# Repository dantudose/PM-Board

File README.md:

# PM-Board

## Embedded development board with ATmega324P

This is a development board supporting the ATmega324P microcontroller. It is fully Arduino-compatible and it comes with the following features:
* LSM9DS0 9-axis inertial sensor (accelerometer, gyroscope and magnetometer)
* MPL3115 baro-altimeter sensor
* Ambient temperature and light sensors
* 128x160 ST7735 color LCD display with SD card reader 
* RGB LED
* 16x02 character LCD display
* GPIO LEDs and pushbuttons
* JTAG and ISP connectors
* USB programming and data interface

<div id="cover">

</div>

## Repository Contents

* **/Code** - Test code for the board (PlatformIO)
* **/Hardware** - Eagle design files (.brd, .sch)
* **/Images** - Board images
* **/bin** - Binaries (board bootloader)

## Programming

### avr-gcc & Makefile

#### Bootloader
The board comes pre-loaded with a bootloader. If you need to re-write it, connect an AVR-ISP or JTAG to the corresponding port and burn the <a href="https://github.com/dantudose/PM-Board/tree/main/bin">bootloader</a> .hex file with _atmega324p_ as a target and the following fuse settings:

<table>
<thead>
  <tr>
    <th>Fuse</th>
    <th>Value</th>
  </tr>
</thead>
<tbody>
  <tr>
    <td>HIGH</td>
    <td>0xDA</td>
  </tr>
  <tr>
    <td>LOW</td>
    <td>0xD7</td>
  </tr>
  <tr>
    <td>EXT</td>
    <td>0XFD</td>
  </tr>
</tbody>
</table>

#### Writing a simple Hello World

Install avr-gcc on your machine. There are various tutorials on how to do this. Here are some examples, depending on your OS type:
* <a href="https://tinusaur.com/guides/avr-gcc-toolchain/">Windows</a>
* <a href="https://baremetalmicro.com/tutorial_avr_toolchain/03-Install-on-Ubuntu-Linux.html">Linux</a>
* <a href="https://wellys.com/posts/avr_c_macos/">Mac</a>

Copy this code into your favourite code editor and save the file as "hello.c":

```cpp
#include <avr/io.h>
#include <util/delay.h>
 
int main() {
	/* Setting PC0 as output */
	DDRC |= (1 << PC0);
 
	while(1) {
                /* Toggle pin state */
		PORTC ^= (1 << PC0);
 
                _delay_ms(500);
	}
 
	return 0;
}

```
To build and upload, you can use the following Makefile. Edit the port to correspond with your OS and serial port name:

```Makefile
# Linux
PORT ?= /dev/ttyUSB0
# Windows
# PORT ?= COM1
 
all: hello.hex
 
hello.hex: hello.elf
	avr-objcopy  -j .text -j .data -O ihex $^ $@
	avr-size hello.elf
 
hello.elf: hello.c
	avr-g++ -mmcu=atmega324p -DF_CPU=12000000 -Os -Wall -o $@ $^
 
upload: hello.hex
	avrdude -c urclock -P $(PORT) -b 57600 -p atmega324p -D -xnometadata -U flash:w:$<:a
 
clean:
	rm -rf hello.elf hello.hex
```

From your command line call _> make all_ (generates hello.hex) and then _> make upload_.

### Arduino

The board can be programmed using <a href="https://github.com/MCUdude/MightyCore">Mighty-Core</a>. 

Follow the "How to install" guide on their github page and use the following settings when burning the bootloader and uploading a sketch:

### PlatformIO (VSCode)

Use the /Code project as reference. 

## Board Pinout

#### LCD Displays

<table>
<thead>
  <tr>
    <th>Character LCD</th>
    <th>GPIO Pin</th>
    <th>Arduino Pin</th>
    <th></th>
    <th>Graphical LCD</th>
    <th>GPIO Pin</th>
    <th>Arduino Pin</th>
  </tr>
</thead>
<tbody>
  <tr>
    <td>RS</td>
    <td>PC0</td>
    <td>16</td>
    <td></td>
    <td>CS</td>
    <td>PB0</td>
    <td>0</td>
  </tr>
  <tr>
    <td>RW</td>
    <td>PC1</td>
    <td>17</td>
    <td></td>
    <td>RST</td>
    <td>PB1</td>
    <td>1</td>
  </tr>
  <tr>
    <td>EN</td>
    <td>PC2</td>
    <td>18</td>
    <td></td>
    <td>A0</td>
    <td>PB4</td>
    <td>4</td>
  </tr>
  <tr>
    <td>D4</td>
    <td>PC3</td>
    <td>19</td>
    <td></td>
    <td>SDA</td>
    <td>PB5</td>
    <td>5</td>
  </tr>
  <tr>
    <td>D5</td>
    <td>PC4</td>
    <td>20</td>
    <td></td>
    <td>SCK</td>
    <td>PB7</td>
    <td>7</td>
  </tr>
  <tr>
    <td>D6</td>
    <td>PC5</td>
    <td>21</td>
    <td></td>
    <td>Backlight</td>
    <td>PA7</td>
    <td>31</td>
  </tr>
  <tr>
    <td>D7</td>
    <td>PC6</td>
    <td>22</td>
    <td></td>
    <td></td>
    <td></td>
    <td></td>
  </tr>
  <tr>
    <td>Backlight</td>
    <td>PC7</td>
    <td>23</td>
    <td></td>
    <td></td>
    <td></td>
    <td></td>
  </tr>
</tbody>
</table>

#### I2C Sensors & Bus Addresses

<table style="float: left; width: 584.312px;">
<tbody>
<tr>
<td style="width: 76px;">&nbsp;<strong>I2C</strong></td>
<td style="width: 103px;"><strong>&nbsp;GPIO Pin</strong>&nbsp;</td>
<td style="width: 94px;"><strong>&nbsp;Arduino Pin</strong>&nbsp;</td>
<td style="width: 35px;">&nbsp;</td>
<td style="width: 98px;"><strong>&nbsp;Chip</strong>&nbsp;</td>
<td style="width: 162.312px;"><strong>&nbsp;Address</strong>&nbsp;</td>
</tr>
<tr>
<td style="width: 76px;">&nbsp;I2C Enable&nbsp;</td>
<td style="width: 103px;">&nbsp;PA6</td>
<td style="width: 94px;">&nbsp;30</td>
<td style="width: 35px;">&nbsp;</td>
<td style="width: 98px;">&nbsp;LSM9DS0&nbsp;</td>
<td style="width: 162.312px;">&nbsp;0x1D (XM) 0x6B (G)</td>
</tr>
<tr>
<td style="width: 76px;">&nbsp;SCL&nbsp;</td>
<td style="width: 103px;">&nbsp;PC0&nbsp;</td>
<td style="width: 94px;">&nbsp;16</td>
<td style="width: 35px;">&nbsp;</td>
<td style="width: 98px;">&nbsp;MPL3115A2&nbsp;</td>
<td style="width: 162.312px;">&nbsp;0x60&nbsp;</td>
</tr>
<tr>
<td style="width: 76px;">&nbsp;SDA&nbsp;</td>
<td style="width: 103px;">&nbsp;PC1&nbsp;</td>
<td style="width: 94px;">&nbsp;17&nbsp;</td>
<td style="width: 35px;">&nbsp;</td>
<td style="width: 98px;">&nbsp;</td>
<td style="width: 162.312px;">&nbsp;</td>
</tr>
</tbody>
</table>
<!-- DivTable.com -->

#### SD Card

<table style="float: left;">
<tbody>
<tr>
<td>&nbsp;<b> </b>&nbsp;</td>
<td>&nbsp;<b>GPIO Pin</b>&nbsp;</td>
<td>&nbsp;<b>Arduino Pin</b>&nbsp;</td>
</tr>
<tr>
<td>&nbsp;CS</td>
<td>&nbsp;PA2</td>
<td>&nbsp;26</td>
</tr>
<tr>
<td>&nbsp;MOSI&nbsp;</td>
<td>&nbsp;PB5&nbsp;</td>
<td>&nbsp;5&nbsp;</td>
</tr>
<tr>
<td>&nbsp;MISO&nbsp;</td>
<td>&nbsp;PB6&nbsp;</td>
<td>&nbsp;6&nbsp;</td>
</tr>
<tr>
<td>&nbsp;SCK&nbsp;</td>
<td>&nbsp;PB7&nbsp;</td>
<td>&nbsp;7&nbsp;</td>
</tr>
</tbody>
</table>
<!-- DivTable.com -->

#### RGB LED

<table class="tg">
<thead>
  <tr>
    <th class="tg-amwm"> </th>
    <th class="tg-amwm">GPIO Pin</th>
    <th class="tg-amwm">Arduino Pin</th>
  </tr>
</thead>
<tbody>
  <tr>
    <td class="tg-hmp3">Red</td>
    <td class="tg-hmp3">PD5</td>
    <td class="tg-hmp3">13</td>
  </tr>
  <tr>
    <td class="tg-0lax">Green</td>
    <td class="tg-0lax">PD7</td>
    <td class="tg-0lax">15</td>
  </tr>
  <tr>
    <td class="tg-hmp3">Blue</td>
    <td class="tg-hmp3">PB3</td>
    <td class="tg-hmp3">3</td>
  </tr>
</tbody>
</table>

### Miscellaneous

<table class="tg">
<thead>
  <tr>
    <th class="tg-0lax"></th>
    <th class="tg-amwm">GPIO Pin</th>
    <th class="tg-amwm">Arduino Pin</th>
  </tr>
</thead>
<tbody>
  <tr>
    <td class="tg-0lax">Temperature Sensor</td>
    <td class="tg-0lax">PA0</td>
    <td class="tg-0lax">A0</td>
  </tr>
  <tr>
    <td class="tg-0lax">Ambient Light Sensor</td>
    <td class="tg-0lax">PA1</td>
    <td class="tg-0lax">A1</td>
  </tr>
  <tr>
    <td class="tg-0lax">BUTTON 1 (PB2)</td>
    <td class="tg-0lax">PB2</td>
    <td class="tg-0lax">2</td>
  </tr>
  <tr>
    <td class="tg-0lax">BUTTON 2 (PD6)</td>
    <td class="tg-0lax">PD6</td>
    <td class="tg-0lax">14</td>
  </tr>
  <tr>
    <td class="tg-0lax">Buttons (BTN1 - 6)</td>
    <td class="tg-0lax">PA5</td>
    <td class="tg-0lax">A5</td>
  </tr>
  <tr>
    <td class="tg-0lax">Speaker</td>
    <td class="tg-0lax">PD4</td>
    <td class="tg-0lax">12</td>
  </tr>
</tbody>
</table>

## License Information

This product is _**open source**_! 

Please review the LICENSE file for license information. 

Distributed as-is; no warranty is given.

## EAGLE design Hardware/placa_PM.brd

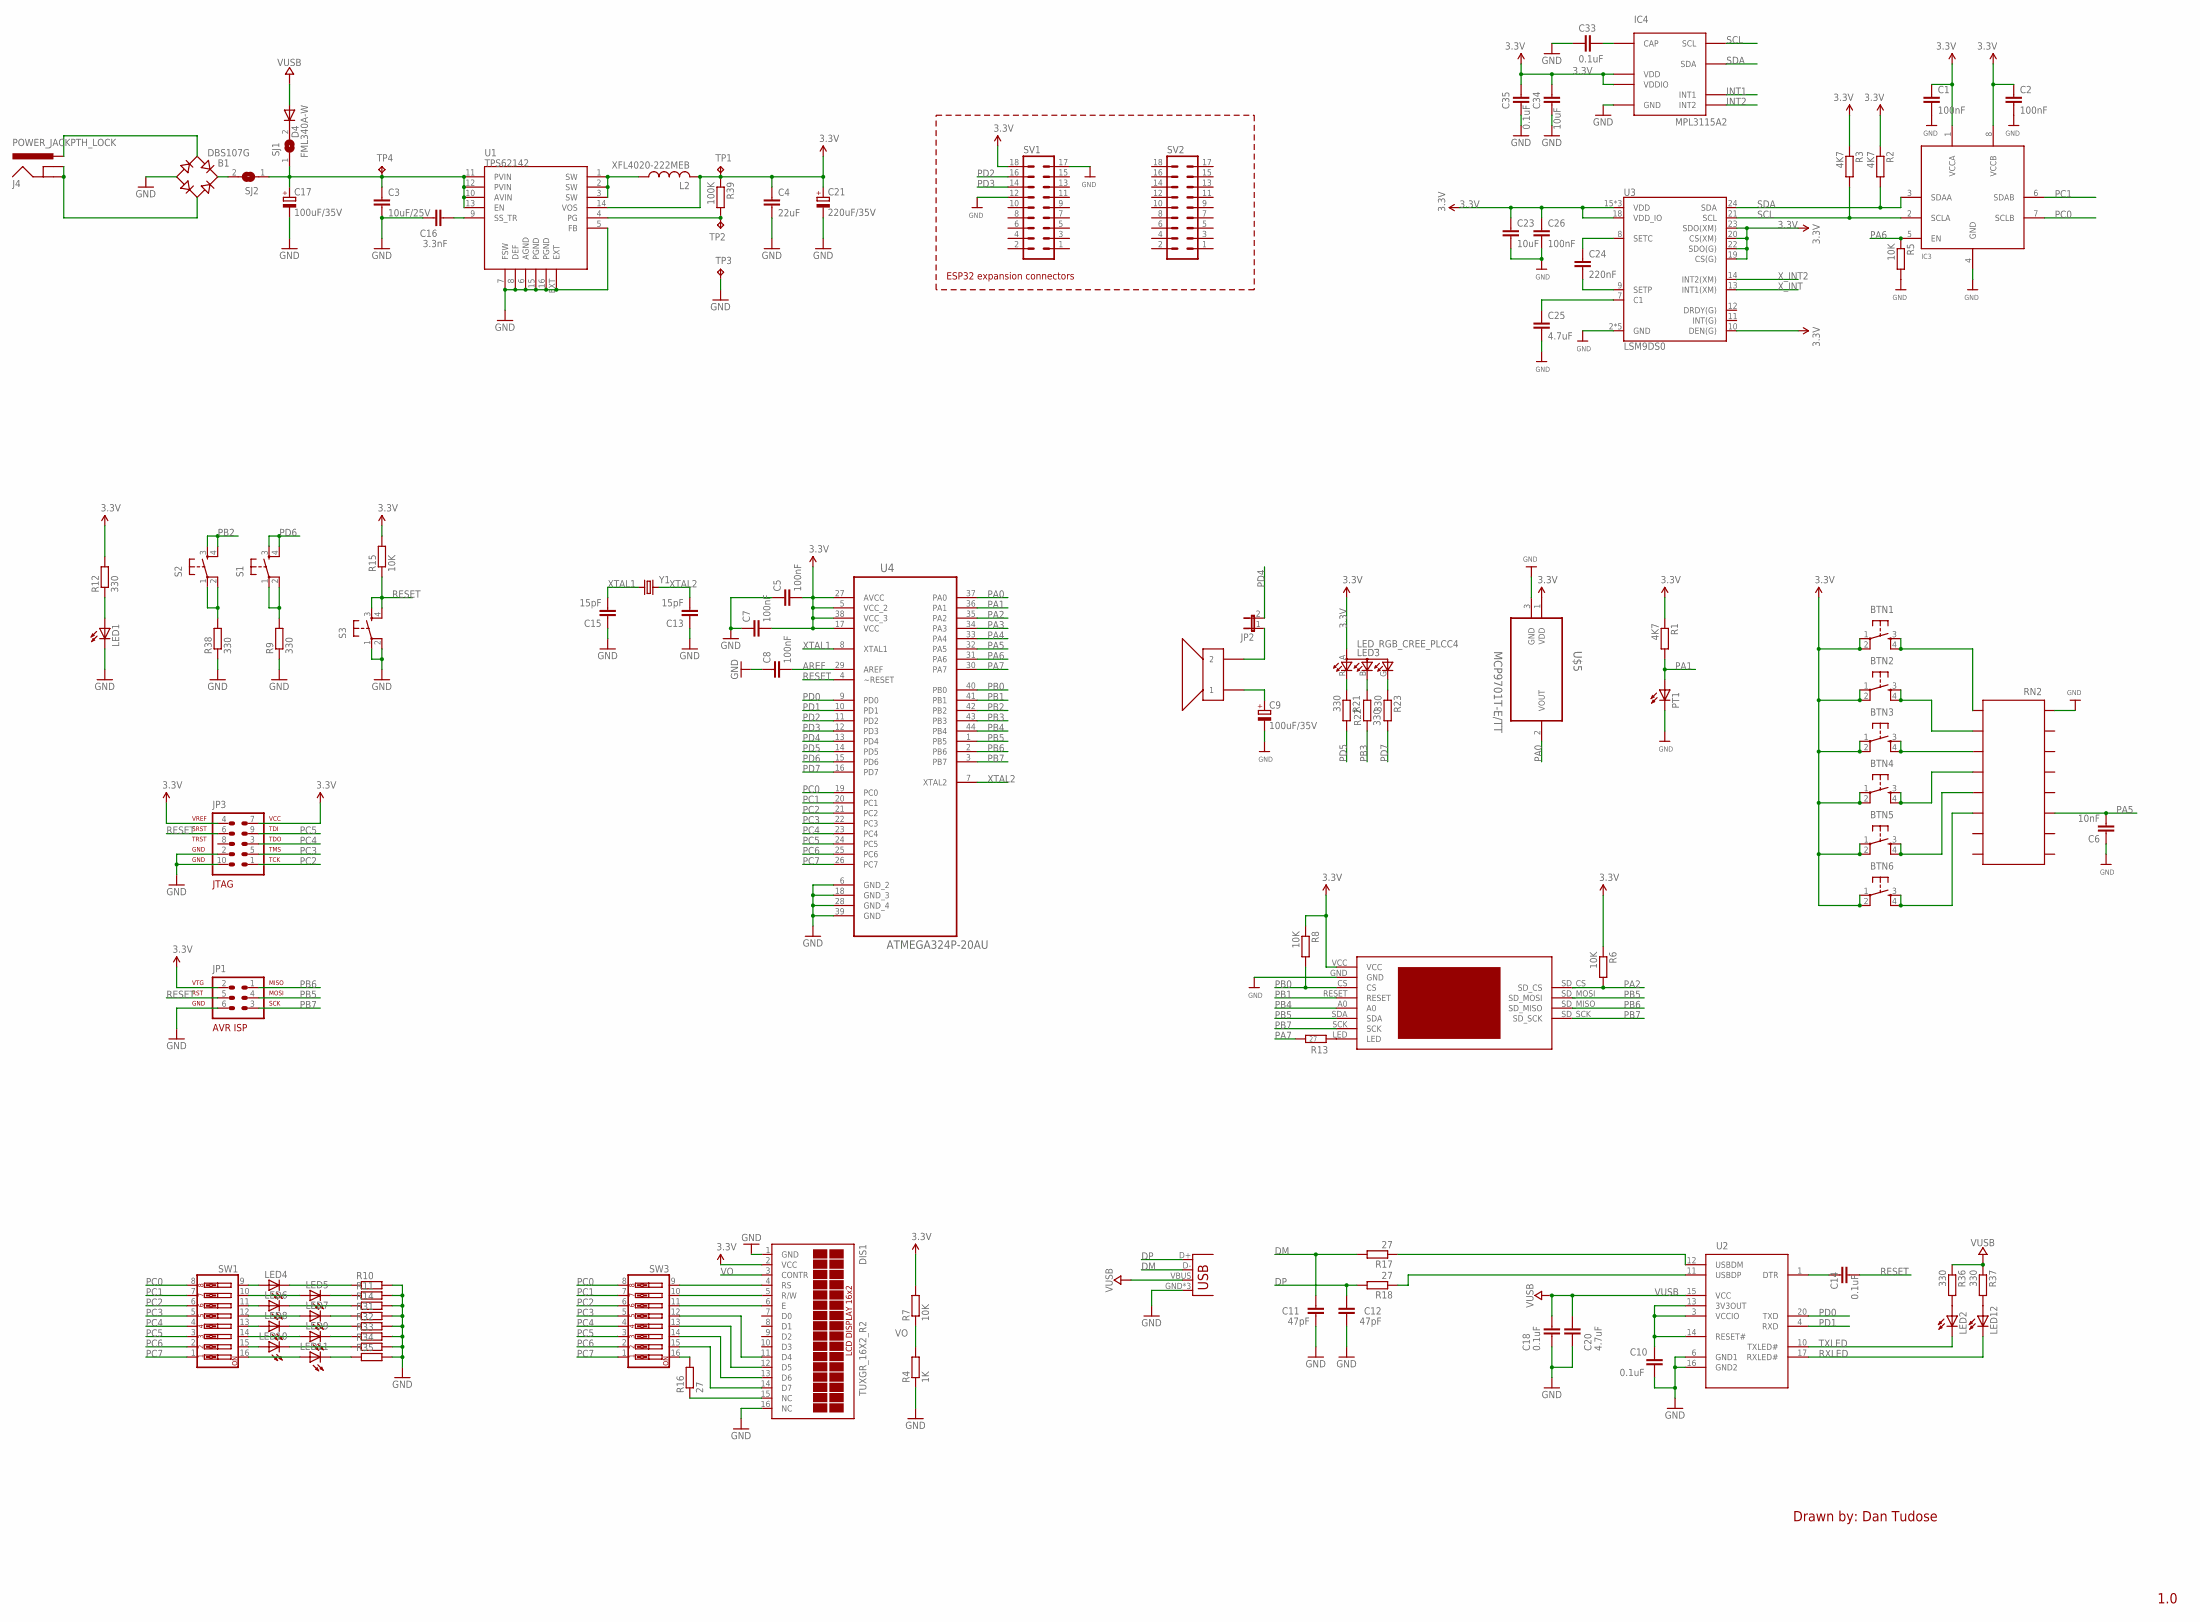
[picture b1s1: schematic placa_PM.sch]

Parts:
B1: DBS107G; DBS
BTN1, BTN2, BTN3, BTN4, BTN5, BTN6: TAC_SWITCHPTH; TACTILE-PTH
C1, C2, C5, C7, C8, C26: 100nF; C0402
C3: 10uF/25V; C1210
C4: 22uF; C1206
C6: 10nF; C0402
C9, C17: 100uF/35V; UD-6,3X7,7_NICHICON
C10, C14, C18: 0.1uF; C0402
C11, C12: 47pF; C0402
C13, C15: 15pF; C0402
C16: 3.3nF; C0603
C20, C25: 4.7uF; C0603
C21: 220uF/35V; UD-6,3X7,7_NICHICON
C23: 10uF; C0402
C24: 220nF; C0402
C33, C35: 0.1uF; 0402-CAP
C34: 10uF; 0402-CAP
D4: FML340A-W; DO-214AC
DIS1: TUXGR_16X2_R2
IC3: TCA9803VSS; VSSOP8
IC4: MPL3115A2; LGA8R125P0X4_500X300X120
J3: USBPTH; USB-B-PTH
J4: POWER_JACKPTH_LOCK; POWER_JACK_PTH_LOCK
JP1: AVR-ISP-6
JP2: JP1E; JP1
JP3: AVR-JTAG-10
L2: XFL4020-222MEB; XFL4020
LED1: LEDCHIPLED_0603; CHIPLED_0603
LED2, LED4, LED5, LED6, LED7, LED8, LED9, LED10, LED11, LED12: LEDCHIP-LED0603; CHIP-LED0603
LED3: LED_RGB_CREE_PLCC4; P-LCC-4-4
PT1: LEDSML0805; SML0805
R1, R2, R3: 4K7; R0402
R4: 1K; R0402
R5, R6, R7, R8, R15: 10K; R0402
R9, R12, R21, R22, R23, R36, R37, R38: 330; R0402
R10, R11, R14, R31, R32, R33, R34, R35: R-EU_R0402; R0402
R13, R16, R17, R18: 27; R0603
R39: 100K; R0402
RN2: 4816P-R2R; 4816P
S1, S2, S3: TAC_SWITCHPTH; TACTILE-PTH
SJ1, SJ2: SJ
SV1, SV2: MA09-2
SW1, SW3: SW_DIP-8; EDG-08
TP1, TP2, TP3, TP4: TPB1,27; B1,27
U1: TPS62142; QFN16-3X3MM_1:1_V03
U2: FT231XS; SSOP20
U3: LSM9DS0; LGA-24
U4: ATMEGA324P-20AU; QFP80P1200X1200X120-44N
U$5: MCP9701T-E/TT; SOT95P237X112-3N
U$6: CVS-3108; SPK
U$8: LCD128X160
Y1: CRYSTAL5X3; CRYSTAL-SMD-5X3

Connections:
3.3V: BTN1.1, BTN1.2, BTN2.1, BTN2.2, BTN3.1, BTN3.2, BTN4.1, BTN4.2, BTN5.1, BTN5.2, BTN6.1, BTN6.2, C1.1, C2.1, C4.1, C5.2, C7.2, C21.+, C23.1, C26.1, C34.2, C35.2, DIS1.2 (VCC), IC3.1 (VCCA), IC3.8 (VCCB), IC4.1 (VDD), IC4.4 (VDDIO), JP1.2, JP3.4, JP3.7, L2.P$2 (2), LED3.A (A2), R1.1, R2.1, R3.1, R6.1, R7.2, R8.1, R12.2, R15.2, R39.1, SV1.18, TP1.TP, U1.14 (VOS), U3.10 (DEN(G)), U3.15 (VDD), U3.16 (VDD), U3.17 (VDD), U3.18 (VDD_IO), U3.19 (CS(G)), U3.20 (CS(XM)), U3.22 (SDO(G)), U3.23 (SDO(XM)), U4.5 (VCC_2), U4.17 (VCC), U4.27 (AVCC), U4.38 (VCC_3), U$5.1 (VDD), U$8.VCC
AREF: C8.2, U4.29 (AREF)
DM: C11.2, J3.D-, R17.2
DP: C12.2, J3.D+, R18.2
GND: B1.-, C1.2, C2.2, C3.2, C4.2, C5.1, C6.1, C7.1, C8.1, C9.-, C10.2, C11.1, C12.1, C13.1, C15.1, C16.1, C17.-, C18.2, C20.2, C21.-, C23.2, C25.2, C26.2, C33.1, C34.1, C35.1, DIS1.1 (GND), DIS1.16 (NC), IC3.4 (GND), IC4.3 (GND), J3.GND, J3.P$1 (GND), J3.P$2 (GND), JP1.6, JP3.2, JP3.10, LED1.C, PT1.C, R4.1, R5.2, R9.1, R10.2, R11.2, R14.2, R31.2, R32.2, R33.2, R34.2, R35.2, R38.1, RN2.9, S3.1, S3.2, SV1.12, SV1.17, TP3.TP, U1.5 (FB), U1.6 (AGND), U1.7 (FSW), U1.8 (DEF), U1.15 (PGND), U1.16 (PGND), U1.EXT, U2.6 (GND1), U2.16 (GND2), U3.2 (GND), U3.3 (GND), U3.4 (GND), U3.5 (GND), U3.6 (GND), U4.6 (GND_2), U4.18 (GND_3), U4.28 (GND_4), U4.39 (GND), U$5.3 (GND), U$8.GND
INT1: IC4.6 (INT1)
INT2: IC4.5 (INT2)
unnamed: BTN1.3, BTN1.4, RN2.8
unnamed: LED1.A, R12.1
unnamed: JP2.1, U$6.P$2 (2)
unnamed: BTN2.3, BTN2.4, RN2.7
unnamed: DIS1.4 (RS), SW3.9
unnamed: C9.+, U$6.P$1 (1)
unnamed: DIS1.5 (R/W), SW3.10
unnamed: DIS1.15 (NC), R16.1
unnamed: R38.2, S2.1, S2.2
unnamed: D4.C, SJ1.2
unnamed: B1.AC1, J4.PWR
unnamed: B1.AC2, J4.GND, J4.GNDBREAK
unnamed: C3.1, C17.+, SJ1.1, SJ2.1, TP4.TP, U1.10 (AVIN), U1.11 (PVIN), U1.12 (PVIN), U1.13 (EN)
unnamed: BTN3.3, BTN3.4, RN2.6
unnamed: BTN4.3, BTN4.4, RN2.5
unnamed: DIS1.6 (E), SW3.11
unnamed: R9.2, S1.1, S1.2
unnamed: B1.+, SJ2.2
unnamed: BTN5.3, BTN5.4, RN2.4
unnamed: BTN6.3, BTN6.4, RN2.3
unnamed: R13.2, U$8.LED
unnamed: LED3.R (CRED), R21.1
unnamed: LED3.B (CBLUE), R22.2
unnamed: C14.1, U2.1 (DTR)
unnamed: C33.2, IC4.2 (CAP)
unnamed: LED3.G (CGREEN), R23.1
unnamed: C24.1, U3.8 (SETC)
unnamed: C24.2, U3.9 (SETP)
unnamed: C25.1, U3.7 (C1)
unnamed: DIS1.11 (D4), SW3.12
unnamed: DIS1.12 (D5), SW3.13
unnamed: C16.2, U1.9 (SS_TR)
unnamed: DIS1.13 (D6), SW3.14
unnamed: DIS1.14 (D7), SW3.15
unnamed: R16.2, SW3.16
unnamed: LED4.A, SW1.9
unnamed: LED6.A, SW1.11
unnamed: LED8.A, SW1.13
unnamed: LED10.A, SW1.15
unnamed: LED11.A, SW1.16
unnamed: LED9.A, SW1.14
unnamed: LED7.A, SW1.12
unnamed: LED5.A, SW1.10
unnamed: LED4.C, R10.1
unnamed: LED5.C, R11.1
unnamed: LED6.C, R14.1
unnamed: LED7.C, R31.1
unnamed: LED8.C, R32.1
unnamed: LED9.C, R33.1
unnamed: LED10.C, R34.1
unnamed: LED11.C, R35.1
unnamed: C10.1, U2.3 (VCCIO), U2.13 (3V3OUT), U2.14 (RESET#)
unnamed: R17.1, U2.12 (USBDM)
unnamed: R18.1, U2.11 (USBDP)
unnamed: LED2.A, R36.2
unnamed: LED12.A, R37.2
unnamed: L2.P$1 (1), U1.1 (SW), U1.2 (SW), U1.3 (SW)
unnamed: R39.2, TP2.TP, U1.4 (PG)
PA0: U4.37 (PA0), U$5.2 (VOUT)
PA1: PT1.A, R1.2, U4.36 (PA1)
PA2: R6.2, U4.35 (PA2), U$8.SD_CS
PA3: U4.34 (PA3)
PA4: U4.33 (PA4)
PA5: C6.2, RN2.14, U4.32 (PA5)
PA6: IC3.5 (EN), R5.1, U4.31 (PA6)
PA7: R13.1, U4.30 (PA7)
PB0: R8.2, U4.40 (PB0), U$8.CS
PB1: U4.41 (PB1), U$8.RESET
PB2: S2.3, S2.4, U4.42 (PB2)
PB3: R22.1, U4.43 (PB3)
PB4: U4.44 (PB4), U$8.A0
PB5: JP1.4, U4.1 (PB5), U$8.SDA, U$8.SD_MOSI
PB6: JP1.1, U4.2 (PB6), U$8.SD_MISO
PB7: JP1.3, U4.3 (PB7), U$8.SCK, U$8.SD_SCK
PC0: IC3.7 (SCLB), SW1.8, SW3.8, U4.19 (PC0)
PC1: IC3.6 (SDAB), SW1.7, SW3.7, U4.20 (PC1)
PC2: JP3.1, SW1.6, SW3.6, U4.21 (PC2)
PC3: JP3.5, SW1.5, SW3.5, U4.22 (PC3)
PC4: JP3.3, SW1.4, SW3.4, U4.23 (PC4)
PC5: JP3.9, SW1.3, SW3.3, U4.24 (PC5)
PC6: SW1.2, SW3.2, U4.25 (PC6)
PC7: SW1.1, SW3.1, U4.26 (PC7)
PD0: U2.20 (TXD), U4.9 (PD0)
PD1: U2.4 (RXD), U4.10 (PD1)
PD2: SV1.16, U4.11 (PD2)
PD3: SV1.14, U4.12 (PD3)
PD4: JP2.2, U4.13 (PD4)
PD5: R21.2, U4.14 (PD5)
PD6: S1.3, S1.4, U4.15 (PD6)
PD7: R23.2, U4.16 (PD7)
RESET: C14.2, JP1.5, JP3.6, R15.1, S3.3, S3.4, U4.4 (~RESET)
RXLED: LED12.C, U2.17 (RXLED#)
SCL: IC3.2 (SCLA), IC4.8 (SCL), R3.2, U3.21 (SCL)
SDA: IC3.3 (SDAA), IC4.7 (SDA), R2.2, U3.24 (SDA)
TXLED: LED2.C, U2.10 (TXLED#)
VO: DIS1.3 (CONTR), R4.2, R7.1
VUSB: C18.1, C20.1, D4.A, J3.VBUS, R36.1, R37.1, U2.15 (VCC)
XTAL1: C15.2, U4.8 (XTAL1), Y1.1
XTAL2: C13.2, U4.7 (XTAL2), Y1.3 (2)
X_INT: U3.13 (INT1(XM))
X_INT2: U3.14 (INT2(XM))

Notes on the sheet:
ESP32 expansion connectors
Drawn by: Dan Tudose
1.0

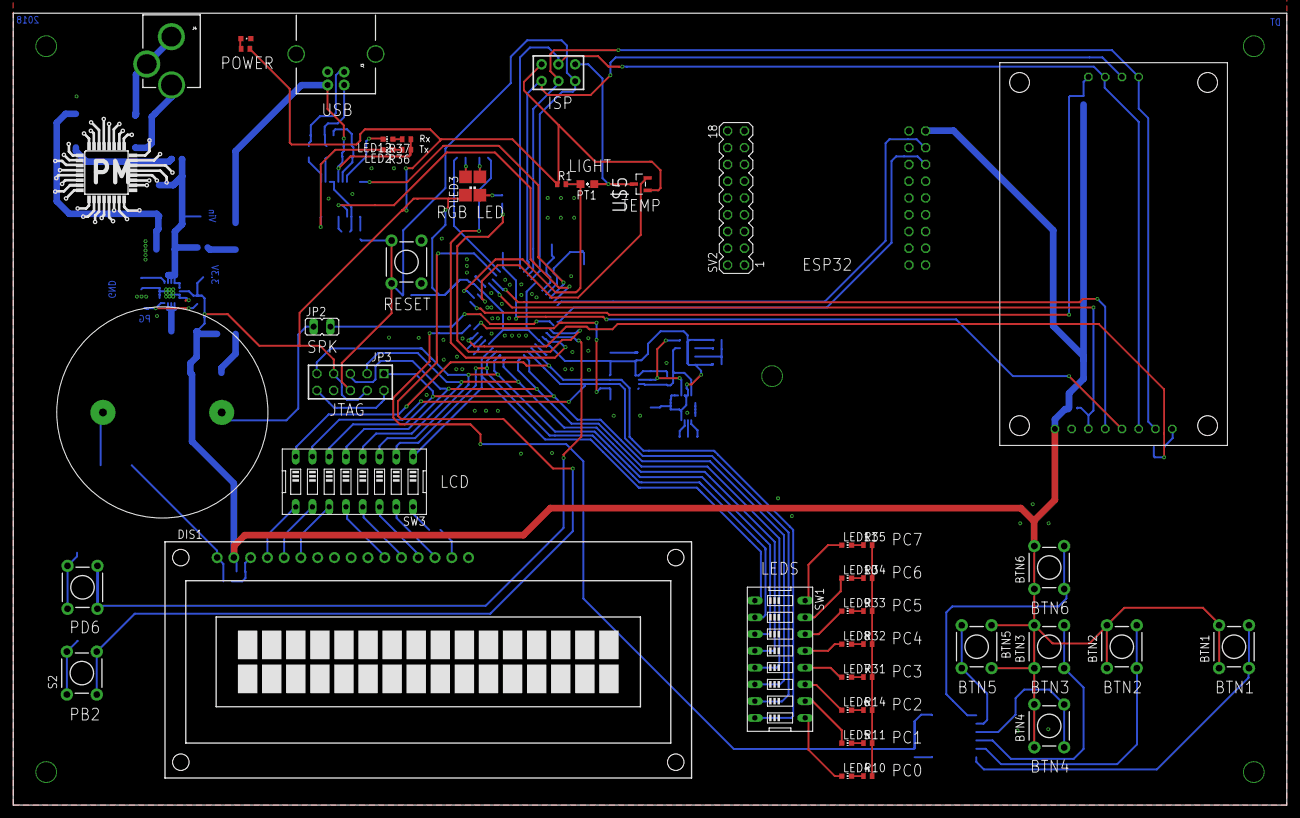
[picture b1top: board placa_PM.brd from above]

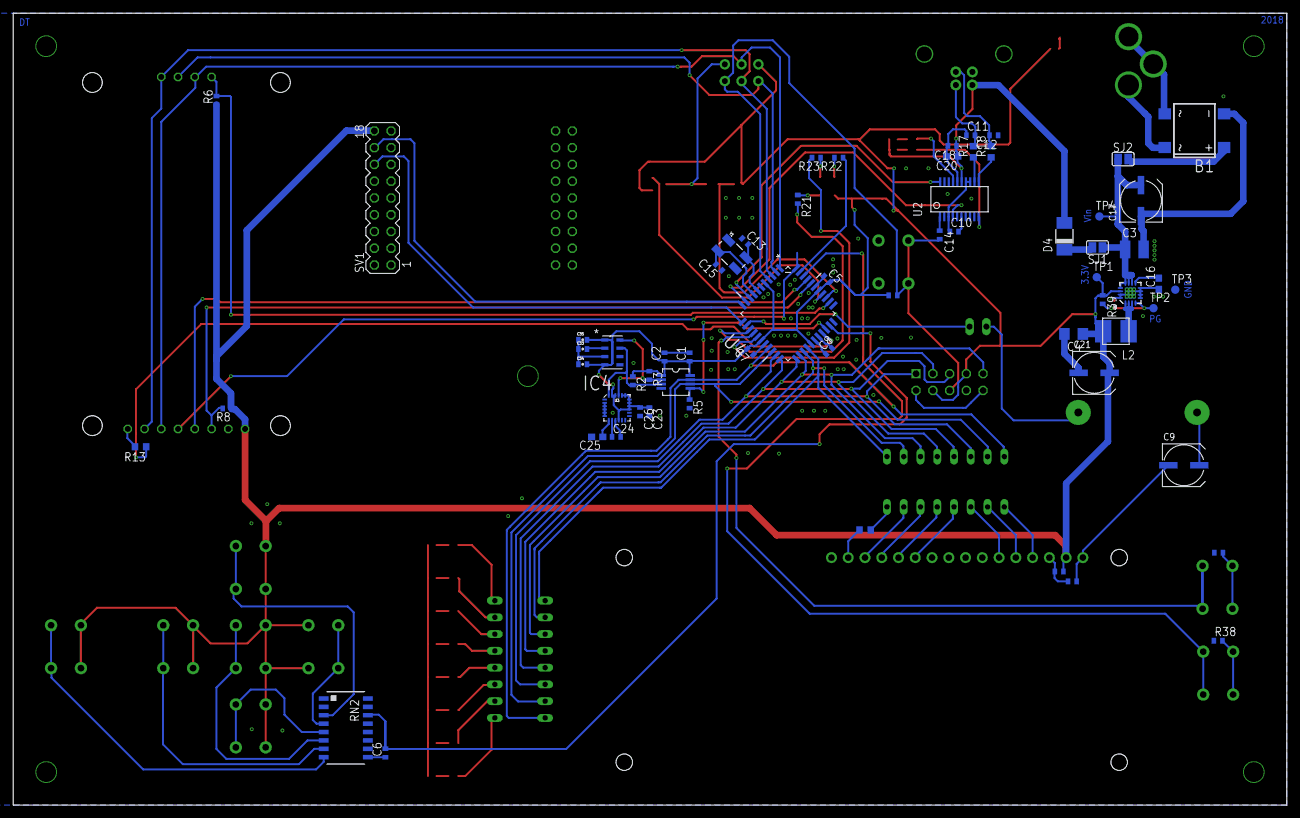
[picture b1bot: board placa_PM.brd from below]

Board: 2 copper layers, 193.0 x 120.0 mm, 109 parts (63 on the bottom side), 102 nets.

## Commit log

2026-02-20 Create bla
2026-02-24 Renamed Buttons 1 & 2

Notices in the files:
parts and their libraries:
SparkFun-Connectors: Licensing: CC v3.0 Share-Alike You are welcome to use this library for commercial purposes.
SparkFun-DigitalIC: Licensing: Creative Commons ShareAlike 4.0 International - https://creativecommons.org/licenses/by-sa/4.0
